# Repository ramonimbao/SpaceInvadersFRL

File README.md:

# Space Invaders FRL

Photo by migfernando#2194

## Disclaimer

Basically, the Space Invaders and the individual Space Invader icons belong solely to Taito Corporation, and cannot be included in this repository. 

## Files

### Case

Case files and drawings are in the `case` folder.

The files are designed for CNC machining and include the drawings for ttap callouts and such. For 3D printing, you may need to modify the files.

### Plate

Plate files are in the `plate` folder.

A DXF file is included for machining/laser cutting.

KiCAD files for an FR4 plate are in the `plate/sifrl-plate` folder. Gerber files are in the `plate/sifrl-plate/JLCPCB/gerbers` folder.

Either way, **order 1mm thick plates**.

### PCB

Main PCB files are in the `pcb` folder.

Gerber files are in the `pcb/JLCPCB/gerbers` folder. Assembly files are in `pcb/JLCPCB/assembly folder`.

A 1.6mm thick PCB should be fine. 1.2mm could work.

### Firmware

The keyboard uses [QMK/VIAL](https://get.vial.today/). Firmware file for it is in the `firmware` folder.

QMK source files for the board are in [this repo](https://github.com/ramonimbao/vial-qmk/tree/kb/sifrl/keyboards/ramonimbao/sifrl).

## Daughterboard

The board uses [my own version of the squatterboard](https://github.com/ramonimbao/squatterboard-v1.5). See the repo for more details.

## Parts Needed

| Qty | Part | URL | Notes |
| --- | ---- | --- | ----- |
| 2   | M3x10 Cap Head Screw | https://www.mcmaster.com/95263A134 | For the case |
| 9   | M2.5x6 Button Head Screw | https://www.mcmaster.com/92095A458 |For the plate |
| 2   | M3x6 Cap Head Screw | https://www.mcmaster.com/92095A179 | For the daughterboard
| 1   | 50mm 4-pin JST-SH cable | https://www.digikey.com/short/q0md9qh8 |  Longer is better if you want to be able to reassemble it often |

## License

The files in this repository are licensed under CERN-OHL-P-2.0. See the LICENSE file for more details.

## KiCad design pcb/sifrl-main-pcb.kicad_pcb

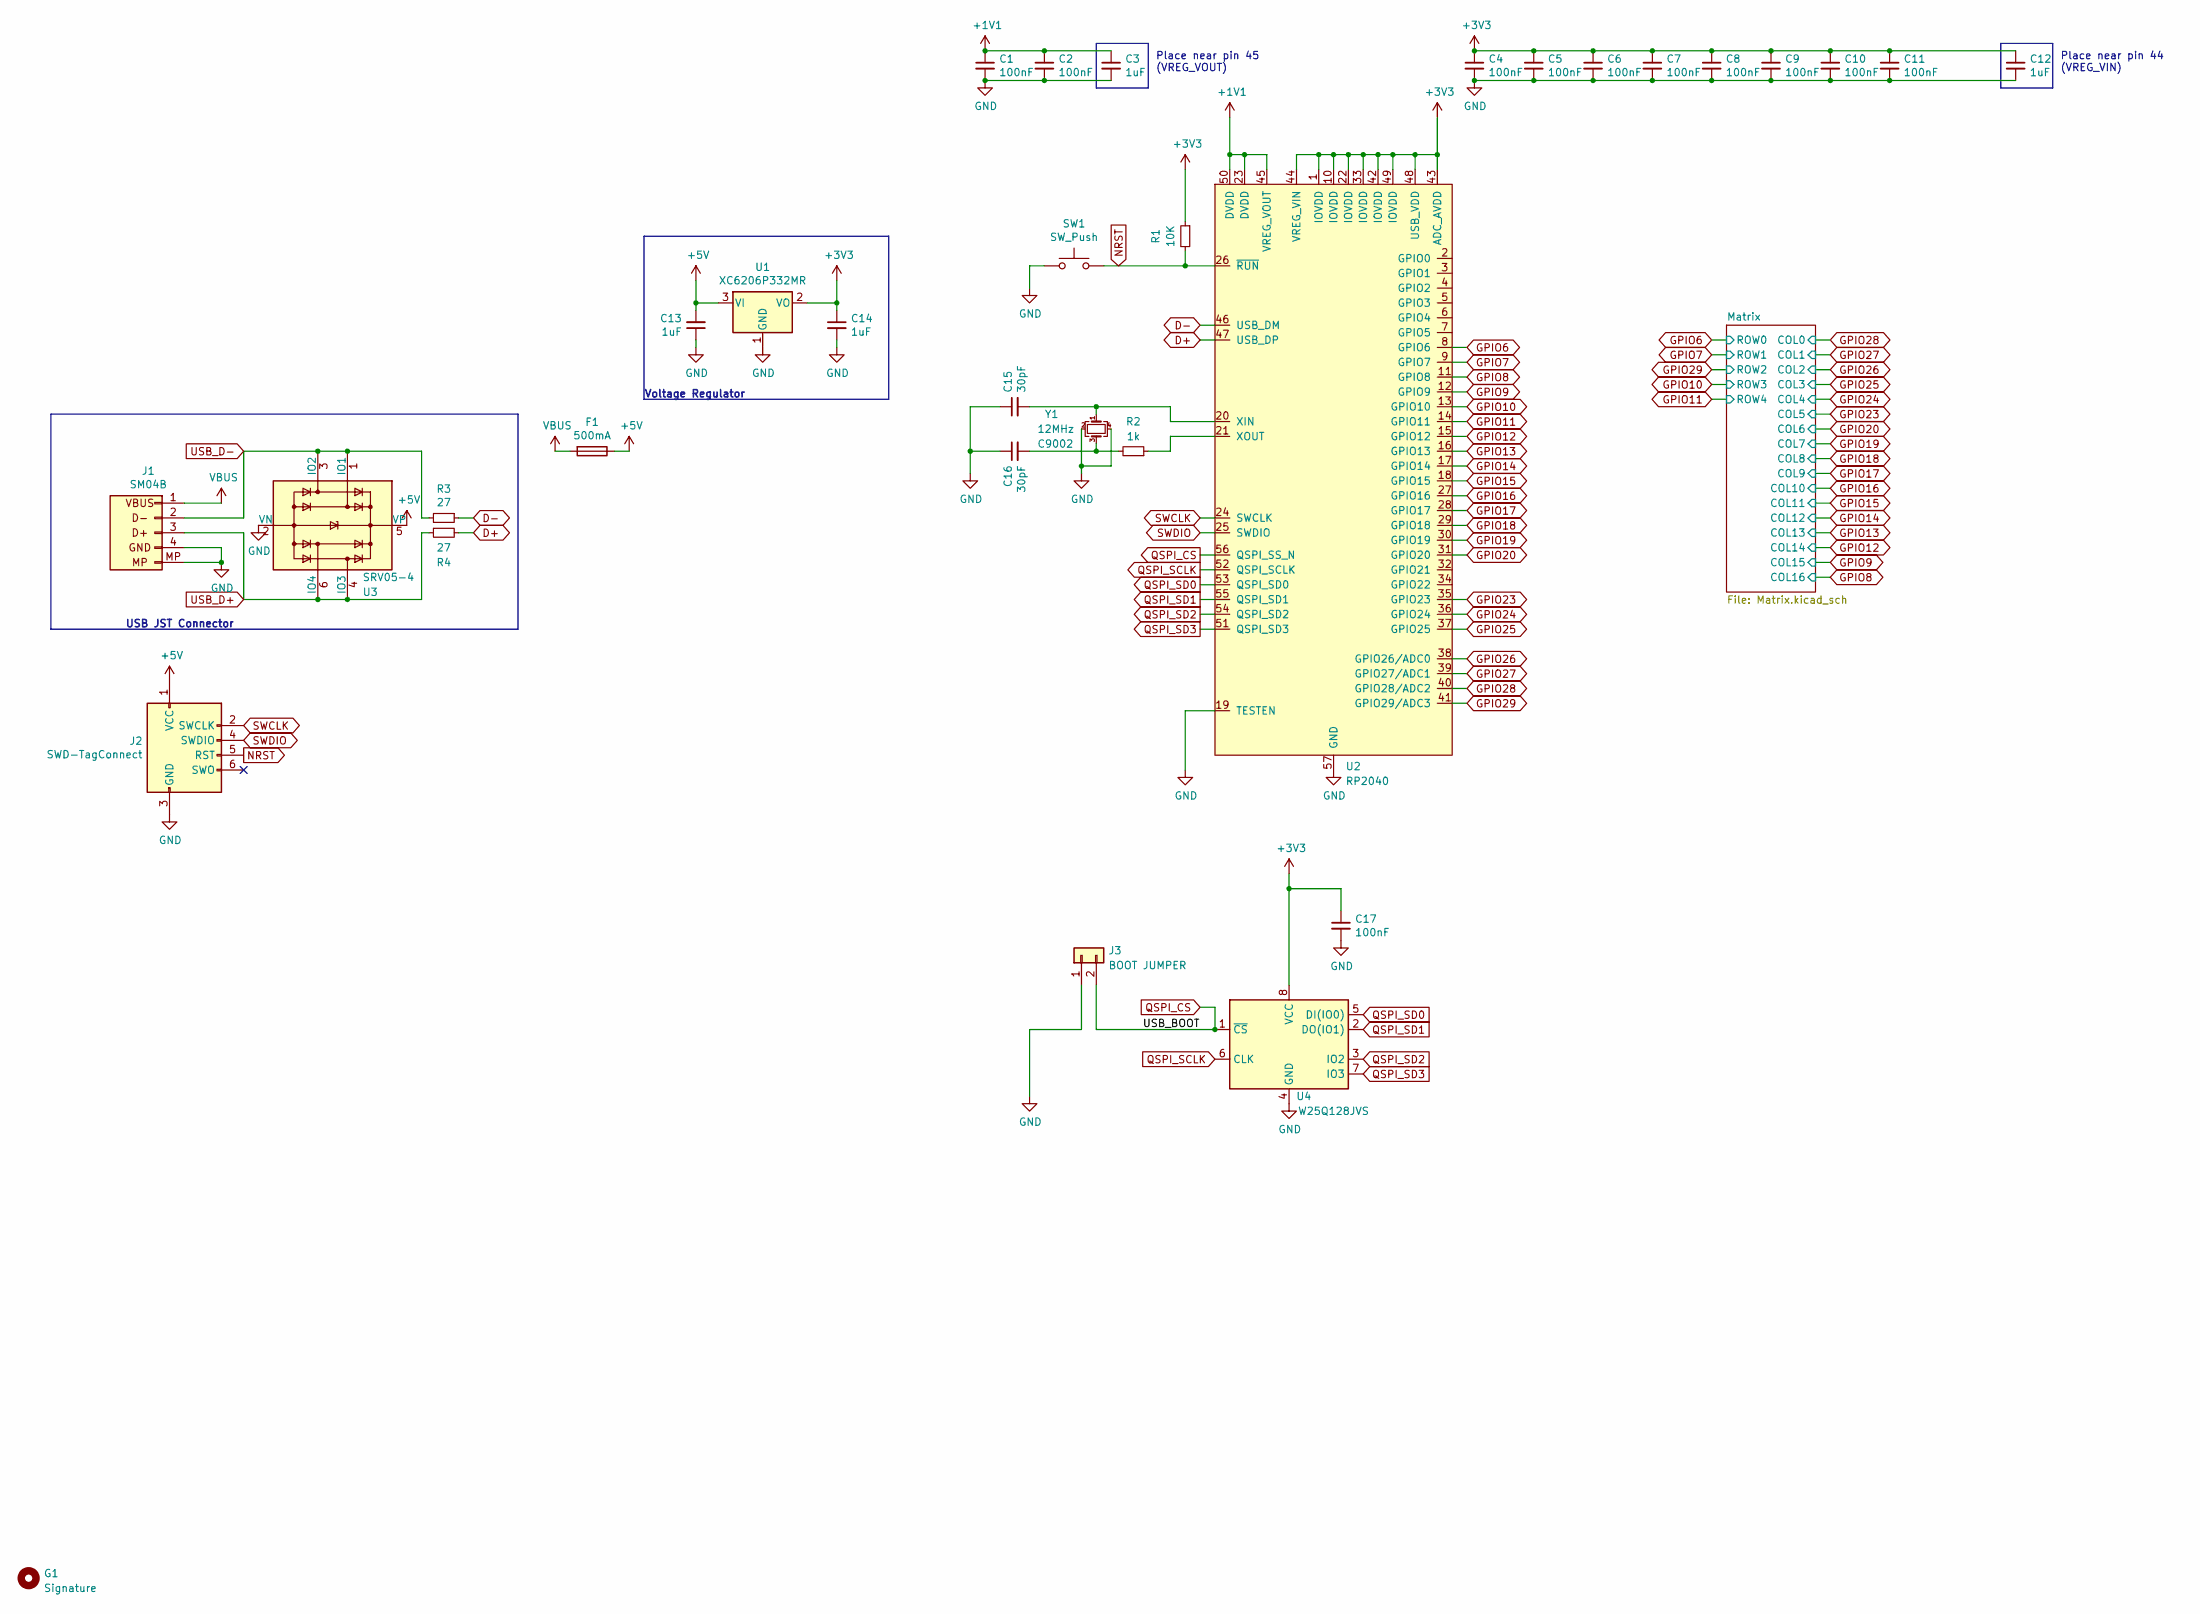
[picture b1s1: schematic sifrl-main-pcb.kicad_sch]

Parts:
C1, C2, C4, C5, C6, C7, C8, C9, C10, C11, C17: 100nF; C_0402_1005Metric
C3, C12, C13, C14: 1uF; C_0603_1608Metric
C15, C16: 30pF; C_0402_1005Metric
F1: 500mA; Fuse_1206_3216Metric_Pad1.42x1.75mm_HandSolder
G1: Signature
J1: SM04B; JST_SH_SM04B-SRSS-TB_1x04-1MP_P1.00mm_Horizontal
J2: SWD-TagConnect; Tag-Connect_TC2030-IDC-NL_2x03_P1.27mm_Vertical
J3: BOOT JUMPER; PinSocket_1x02_P2.54mm_Vertical
R1: 10K; R_0402_1005Metric
R2: 1k; R_0402_1005Metric
R3, R4: 27; R_0603_1608Metric
SW1: SW_Push; SW_SPST_TL3342
U1: XC6206P332MR; SOT-23
U2: RP2040; RP2040-QFN-56
U3: SRV05-4; SOT-23-6
U4: W25Q128JVS; SOIC-8_5.23x5.23mm_P1.27mm
Y1: 12MHz; Crystal_SMD_3225-4Pin_3.2x2.5mm; LCSC C9002

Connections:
+1V1: C1.1, C2.1, C3.1, U2.23 (DVDD), U2.45 (VREG_VOUT), U2.50 (DVDD)
+3V3: C4.1, C5.1, C6.1, C7.1, C8.1, C9.1, C10.1, C11.1, C12.1, C14.1, C17.1, R1.1, U1.2 (VO), U2.1 (IOVDD), U2.10 (IOVDD), U2.22 (IOVDD), U2.33 (IOVDD), U2.42 (IOVDD), U2.43 (ADC_AVDD), U2.44 (VREG_VIN), U2.48 (USB_VDD), U2.49 (IOVDD), U4.8 (VCC)
+5V: C13.2, F1.1, J2.1 (VCC), U1.3 (VI), U3.5 (VP)
D+: R4.2, U2.47 (USB_DP)
D-: R3.1, U2.46 (USB_DM)
GND: C1.2, C2.2, C3.2, C4.2, C5.2, C6.2, C7.2, C8.2, C9.2, C10.2, C11.2, C12.2, C13.1, C14.2, C15.1, C16.1, C17.2, J1.4 (GND), J1.MP (Mounting), J2.3 (GND), J3.1, SW1.1, U1.1 (GND), U2.19 (TESTEN), U2.57 (GND), U3.2 (VN), U4.4 (GND), Y1.2, Y1.4
GPIO6: U2.8 (GPIO6); also elsewhere on the board
GPIO7: U2.9 (GPIO7); also elsewhere on the board
GPIO8: U2.11 (GPIO8); also elsewhere on the board
GPIO9: U2.12 (GPIO9); also elsewhere on the board
GPIO10: U2.13 (GPIO10); also elsewhere on the board
GPIO11: U2.14 (GPIO11); also elsewhere on the board
GPIO12: U2.15 (GPIO12); also elsewhere on the board
GPIO13: U2.16 (GPIO13); also elsewhere on the board
GPIO14: U2.17 (GPIO14); also elsewhere on the board
GPIO15: U2.18 (GPIO15); also elsewhere on the board
GPIO16: U2.27 (GPIO16); also elsewhere on the board
GPIO17: U2.28 (GPIO17); also elsewhere on the board
GPIO18: U2.29 (GPIO18); also elsewhere on the board
GPIO19: U2.30 (GPIO19); also elsewhere on the board
GPIO20: U2.31 (GPIO20); also elsewhere on the board
GPIO23: U2.35 (GPIO23); also elsewhere on the board
GPIO24: U2.36 (GPIO24); also elsewhere on the board
GPIO25: U2.37 (GPIO25); also elsewhere on the board
GPIO26: U2.38 (GPIO26/ADC0); also elsewhere on the board
GPIO27: U2.39 (GPIO27/ADC1); also elsewhere on the board
GPIO28: U2.40 (GPIO28/ADC2); also elsewhere on the board
GPIO29: U2.41 (GPIO29/ADC3); also elsewhere on the board
NRST: J2.5 (RST), R1.2, SW1.2, U2.26 (~RUN)
unnamed: C15.2, U2.20 (XIN), Y1.1
unnamed: C16.2, R2.2, Y1.3
unnamed: R2.1, U2.21 (XOUT)
QSPI_CS: J3.2, U2.56 (QSPI_SS_N), U4.1 (~CS)
QSPI_SCLK: U2.52 (QSPI_SCLK), U4.6 (CLK)
QSPI_SD0: U2.53 (QSPI_SD0), U4.5 (DI(IO0))
QSPI_SD1: U2.55 (QSPI_SD1), U4.2 (DO(IO1))
QSPI_SD2: U2.54 (QSPI_SD2), U4.3 (IO2)
QSPI_SD3: U2.51 (QSPI_SD3), U4.7 (IO3)
SWCLK: J2.2 (SWCLK), U2.24 (SWCLK)
SWDIO: J2.4 (SWDIO), U2.25 (SWDIO)
USB_D+: J1.3 (D+), R4.1, U3.4 (IO3), U3.6 (IO4)
USB_D-: J1.2 (D-), R3.2, U3.1 (IO1), U3.3 (IO2)
VBUS: F1.2, J1.1 (VBUS)

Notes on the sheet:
Voltage Regulator
Place near pin 45 (VREG_VOUT)
USB JST Connector
Place near pin 44 (VREG_VIN)

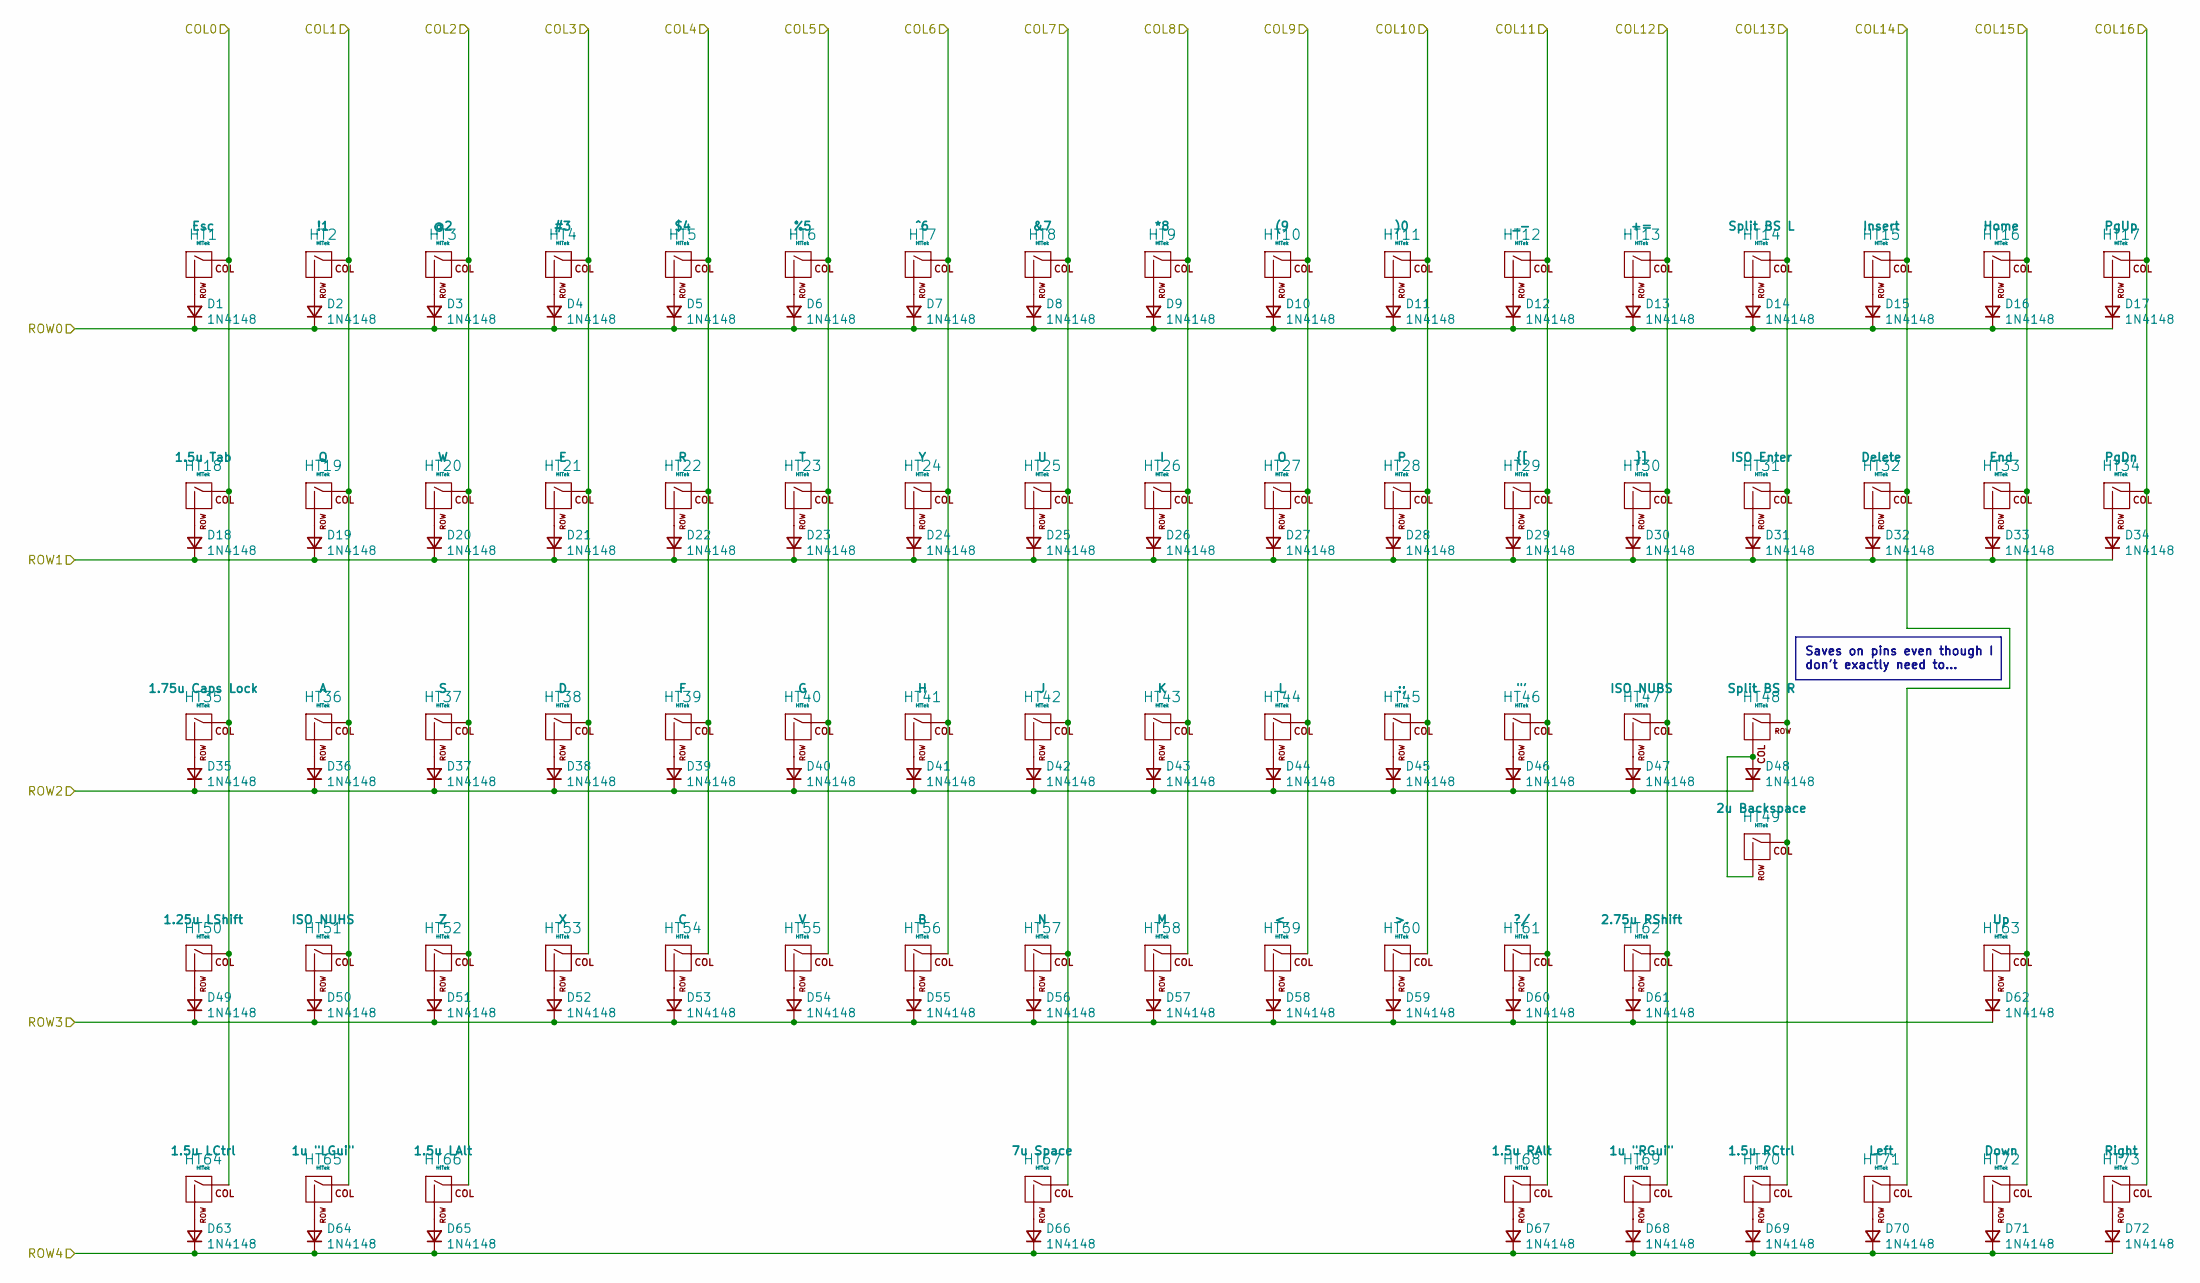
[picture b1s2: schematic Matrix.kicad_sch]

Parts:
D1, D2, D3, D4, D5, D6, D7, D8, D9, D10, D11, D12, D13, D14, D15, D16, D17, D18, D19, D20, D21, D22, D23, D24, D25, D26, D27, D28, D29, D30, D31, D32, D33, D34, D35, D36, D37, D38, D39, D40, D41, D42, D43, D44, D45, D46, D47, D48, D49, D50, D51, D52, D53, D54, D55, D56, D57, D58, D59, D60, D61, D62, D63, D64, D65, D66, D67, D68, D69, D70, D71, D72: 1N4148; D_SOD-123-Pretty
HT1, HT2, HT3, HT4, HT5, HT6, HT7, HT8, HT9, HT10, HT11, HT12, HT13, HT15, HT16, HT17, HT19, HT20, HT21, HT22, HT23, HT24, HT25, HT26, HT27, HT28, HT29, HT30, HT32, HT33, HT34, HT36, HT37, HT38, HT39, HT40, HT41, HT42, HT43, HT44, HT45, HT46, HT47, HT48, HT51, HT52, HT53, HT54, HT55, HT56, HT57, HT58, HT59, HT60, HT61, HT63, HT65, HT69, HT71, HT72, HT73: HiTek; Hitek725-1U
HT14: HiTek; Hitek725-1U-DudPad
HT18, HT64, HT66, HT68, HT70: HiTek; Hitek725-1.5U
HT31: HiTek; Hitek725-ISO
HT35: HiTek; Hitek725-1.75U
HT49: HiTek; Hitek725-2U-DudPad
HT50: HiTek; Hitek725-1.25U
HT62: HiTek; Hitek725-2.75U
HT67: HiTek; Hitek725-7U

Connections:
GPIO6: D1.1 (K), D2.1 (K), D3.1 (K), D4.1 (K), D5.1 (K), D6.1 (K), D7.1 (K), D8.1 (K), D9.1 (K), D10.1 (K), D11.1 (K), D12.1 (K), D13.1 (K), D14.1 (K), D15.1 (K), D16.1 (K), D17.1 (K); also elsewhere on the board
GPIO7: D18.1 (K), D19.1 (K), D20.1 (K), D21.1 (K), D22.1 (K), D23.1 (K), D24.1 (K), D25.1 (K), D26.1 (K), D27.1 (K), D28.1 (K), D29.1 (K), D30.1 (K), D31.1 (K), D32.1 (K), D33.1 (K), D34.1 (K); also elsewhere on the board
GPIO8: HT17.1 (COL), HT34.1 (COL), HT73.1 (COL); also elsewhere on the board
GPIO9: HT16.1 (COL), HT33.1 (COL), HT63.1 (COL), HT72.1 (COL); also elsewhere on the board
GPIO10: D49.1 (K), D50.1 (K), D51.1 (K), D52.1 (K), D53.1 (K), D54.1 (K), D55.1 (K), D56.1 (K), D57.1 (K), D58.1 (K), D59.1 (K), D60.1 (K), D61.1 (K), D62.1 (K); also elsewhere on the board
GPIO11: D63.1 (K), D64.1 (K), D65.1 (K), D66.1 (K), D67.1 (K), D68.1 (K), D69.1 (K), D70.1 (K), D71.1 (K), D72.1 (K); also elsewhere on the board
GPIO12: HT15.1 (COL), HT32.1 (COL), HT71.1 (COL); also elsewhere on the board
GPIO13: HT14.1 (COL), HT31.1 (COL), HT48.2 (ROW), HT49.1 (COL), HT70.1 (COL); also elsewhere on the board
GPIO14: HT13.1 (COL), HT30.1 (COL), HT47.1 (COL), HT62.1 (COL), HT69.1 (COL); also elsewhere on the board
GPIO15: HT12.1 (COL), HT29.1 (COL), HT46.1 (COL), HT61.1 (COL), HT68.1 (COL); also elsewhere on the board
GPIO16: HT11.1 (COL), HT28.1 (COL), HT45.1 (COL), HT60.1 (COL); also elsewhere on the board
GPIO17: HT10.1 (COL), HT27.1 (COL), HT44.1 (COL), HT59.1 (COL); also elsewhere on the board
GPIO18: HT9.1 (COL), HT26.1 (COL), HT43.1 (COL), HT58.1 (COL); also elsewhere on the board
GPIO19: HT8.1 (COL), HT25.1 (COL), HT42.1 (COL), HT57.1 (COL), HT67.1 (COL); also elsewhere on the board
GPIO20: HT7.1 (COL), HT24.1 (COL), HT41.1 (COL), HT56.1 (COL); also elsewhere on the board
GPIO23: HT6.1 (COL), HT23.1 (COL), HT40.1 (COL), HT55.1 (COL); also elsewhere on the board
GPIO24: HT5.1 (COL), HT22.1 (COL), HT39.1 (COL), HT54.1 (COL); also elsewhere on the board
GPIO25: HT4.1 (COL), HT21.1 (COL), HT38.1 (COL), HT53.1 (COL); also elsewhere on the board
GPIO26: HT3.1 (COL), HT20.1 (COL), HT37.1 (COL), HT52.1 (COL), HT66.1 (COL); also elsewhere on the board
GPIO27: HT2.1 (COL), HT19.1 (COL), HT36.1 (COL), HT51.1 (COL), HT65.1 (COL); also elsewhere on the board
GPIO28: HT1.1 (COL), HT18.1 (COL), HT35.1 (COL), HT50.1 (COL), HT64.1 (COL); also elsewhere on the board
GPIO29: D35.1 (K), D36.1 (K), D37.1 (K), D38.1 (K), D39.1 (K), D40.1 (K), D41.1 (K), D42.1 (K), D43.1 (K), D44.1 (K), D45.1 (K), D46.1 (K), D47.1 (K), D48.1 (K); also elsewhere on the board
unnamed: D1.2 (A), HT1.2 (ROW)
unnamed: D2.2 (A), HT2.2 (ROW)
unnamed: D3.2 (A), HT3.2 (ROW)
unnamed: D4.2 (A), HT4.2 (ROW)
unnamed: D5.2 (A), HT5.2 (ROW)
unnamed: D6.2 (A), HT6.2 (ROW)
unnamed: D7.2 (A), HT7.2 (ROW)
unnamed: D8.2 (A), HT8.2 (ROW)
unnamed: D9.2 (A), HT9.2 (ROW)
unnamed: D10.2 (A), HT10.2 (ROW)
unnamed: D11.2 (A), HT11.2 (ROW)
unnamed: D12.2 (A), HT12.2 (ROW)
unnamed: D13.2 (A), HT13.2 (ROW)
unnamed: D14.2 (A), HT14.2 (ROW)
unnamed: D15.2 (A), HT15.2 (ROW)
unnamed: D16.2 (A), HT16.2 (ROW)
unnamed: D17.2 (A), HT17.2 (ROW)
unnamed: D18.2 (A), HT18.2 (ROW)
unnamed: D19.2 (A), HT19.2 (ROW)
unnamed: D20.2 (A), HT20.2 (ROW)
unnamed: D21.2 (A), HT21.2 (ROW)
unnamed: D22.2 (A), HT22.2 (ROW)
unnamed: D23.2 (A), HT23.2 (ROW)
unnamed: D24.2 (A), HT24.2 (ROW)
unnamed: D25.2 (A), HT25.2 (ROW)
unnamed: D26.2 (A), HT26.2 (ROW)
unnamed: D27.2 (A), HT27.2 (ROW)
unnamed: D28.2 (A), HT28.2 (ROW)
unnamed: D29.2 (A), HT29.2 (ROW)
unnamed: D30.2 (A), HT30.2 (ROW)
unnamed: D31.2 (A), HT31.2 (ROW)
unnamed: D32.2 (A), HT32.2 (ROW)
unnamed: D33.2 (A), HT33.2 (ROW)
unnamed: D34.2 (A), HT34.2 (ROW)
unnamed: D35.2 (A), HT35.2 (ROW)
unnamed: D36.2 (A), HT36.2 (ROW)
unnamed: D37.2 (A), HT37.2 (ROW)
unnamed: D38.2 (A), HT38.2 (ROW)
unnamed: D39.2 (A), HT39.2 (ROW)
unnamed: D40.2 (A), HT40.2 (ROW)
unnamed: D41.2 (A), HT41.2 (ROW)
unnamed: D42.2 (A), HT42.2 (ROW)
unnamed: D43.2 (A), HT43.2 (ROW)
unnamed: D44.2 (A), HT44.2 (ROW)
unnamed: D45.2 (A), HT45.2 (ROW)
unnamed: D46.2 (A), HT46.2 (ROW)
unnamed: D47.2 (A), HT47.2 (ROW)
unnamed: D48.2 (A), HT48.1 (COL), HT49.2 (ROW)
unnamed: D49.2 (A), HT50.2 (ROW)
unnamed: D50.2 (A), HT51.2 (ROW)
unnamed: D51.2 (A), HT52.2 (ROW)
unnamed: D52.2 (A), HT53.2 (ROW)
unnamed: D53.2 (A), HT54.2 (ROW)
unnamed: D54.2 (A), HT55.2 (ROW)
unnamed: D55.2 (A), HT56.2 (ROW)
unnamed: D56.2 (A), HT57.2 (ROW)
unnamed: D57.2 (A), HT58.2 (ROW)
unnamed: D58.2 (A), HT59.2 (ROW)
unnamed: D59.2 (A), HT60.2 (ROW)
unnamed: D60.2 (A), HT61.2 (ROW)
unnamed: D61.2 (A), HT62.2 (ROW)
unnamed: D62.2 (A), HT63.2 (ROW)
unnamed: D63.2 (A), HT64.2 (ROW)
unnamed: D64.2 (A), HT65.2 (ROW)
unnamed: D65.2 (A), HT66.2 (ROW)
unnamed: D66.2 (A), HT67.2 (ROW)
unnamed: D67.2 (A), HT68.2 (ROW)
unnamed: D68.2 (A), HT69.2 (ROW)
unnamed: D69.2 (A), HT70.2 (ROW)
unnamed: D70.2 (A), HT71.2 (ROW)
unnamed: D71.2 (A), HT72.2 (ROW)
unnamed: D72.2 (A), HT73.2 (ROW)

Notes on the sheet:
Saves on pins even though I don't exactly need to...

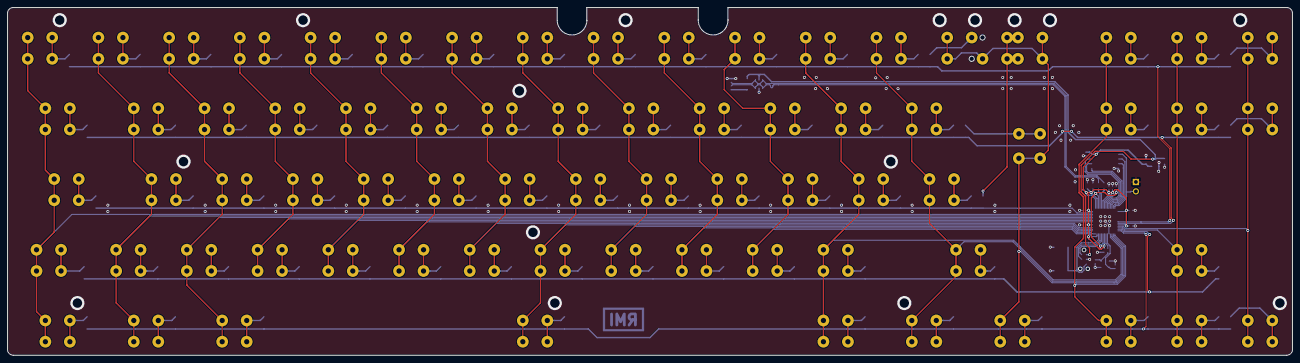
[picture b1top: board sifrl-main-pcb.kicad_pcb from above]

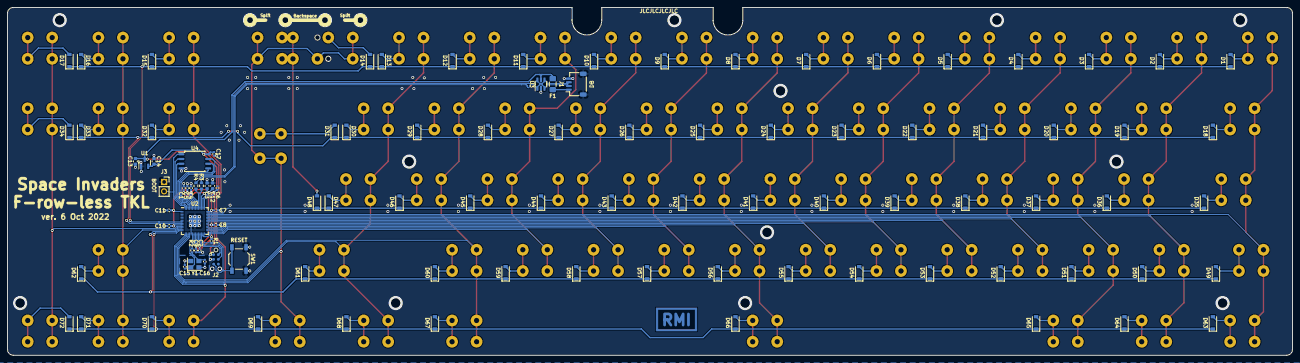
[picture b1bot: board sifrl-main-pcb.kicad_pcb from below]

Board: 2 copper layers, 346.1 x 93.7 mm, 177 parts (104 on the bottom side), 115 nets.

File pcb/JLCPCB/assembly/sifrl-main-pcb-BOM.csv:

Comment,Designator,Footprint,LCSC
100nF,"C1,C2,C4,C5,C6,C7,C8,C9,C10,C11,C17",Capacitor_SMD:C_0402_1005Metric,C1525
30pF,"C15,C16",Capacitor_SMD:C_0402_1005Metric,C1570
1uF,"C3,C12,C13,C14",Capacitor_SMD:C_0603_1608Metric,C15849
1N4148,"D1,D2,D3,D4,D5,D6,D7,D8,D9,D10,D11,D12,D13,D14,D15,D16,D17,D18,D19,D20,D21,D22,D23,D24,D25,D26,D27,D28,D29,D30,D31,D32,D33,D34,D35,D36,D37,D38,D39,D40,D41,D42,D43,D44,D45,D46,D47,D48,D49,D50,D51,D52,D53,D54,D55,D56,D57,D58,D59,D60,D61,D62,D63,D64,D65,D66,D67,D68,D69,D70,D71,D72",random-keyboard-parts:D_SOD-123-Pretty,C81598
500mA,F1,Fuse:Fuse_1206_3216Metric_Pad1.42x1.75mm_HandSolder,C70076
SM04B,J1,Connector_JST:JST_SH_SM04B-SRSS-TB_1x04-1MP_P1.00mm_Horizontal,C160404
10K,R1,Resistor_SMD:R_0402_1005Metric,C25744
1k,R2,Resistor_SMD:R_0402_1005Metric,C11702
27,"R3,R4",Resistor_SMD:R_0603_1608Metric,C25190
SW_Push,SW1,Button_Switch_SMD:SW_SPST_TL3342,C318884
XC6206P332MR,U1,Package_TO_SOT_SMD:SOT-23,C5446
RP2040,U2,random-keyboard-parts:RP2040-QFN-56,C2040
SRV05-4,U3,Package_TO_SOT_SMD:SOT-23-6,C85364
W25Q128JVS,U4,Package_SO:SOIC-8_5.23x5.23mm_P1.27mm,C97521
12MHz,Y1,Crystal:Crystal_SMD_3225-4Pin_3.2x2.5mm,C9002

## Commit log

2022-11-13 Add URLs to where you can buy parts
